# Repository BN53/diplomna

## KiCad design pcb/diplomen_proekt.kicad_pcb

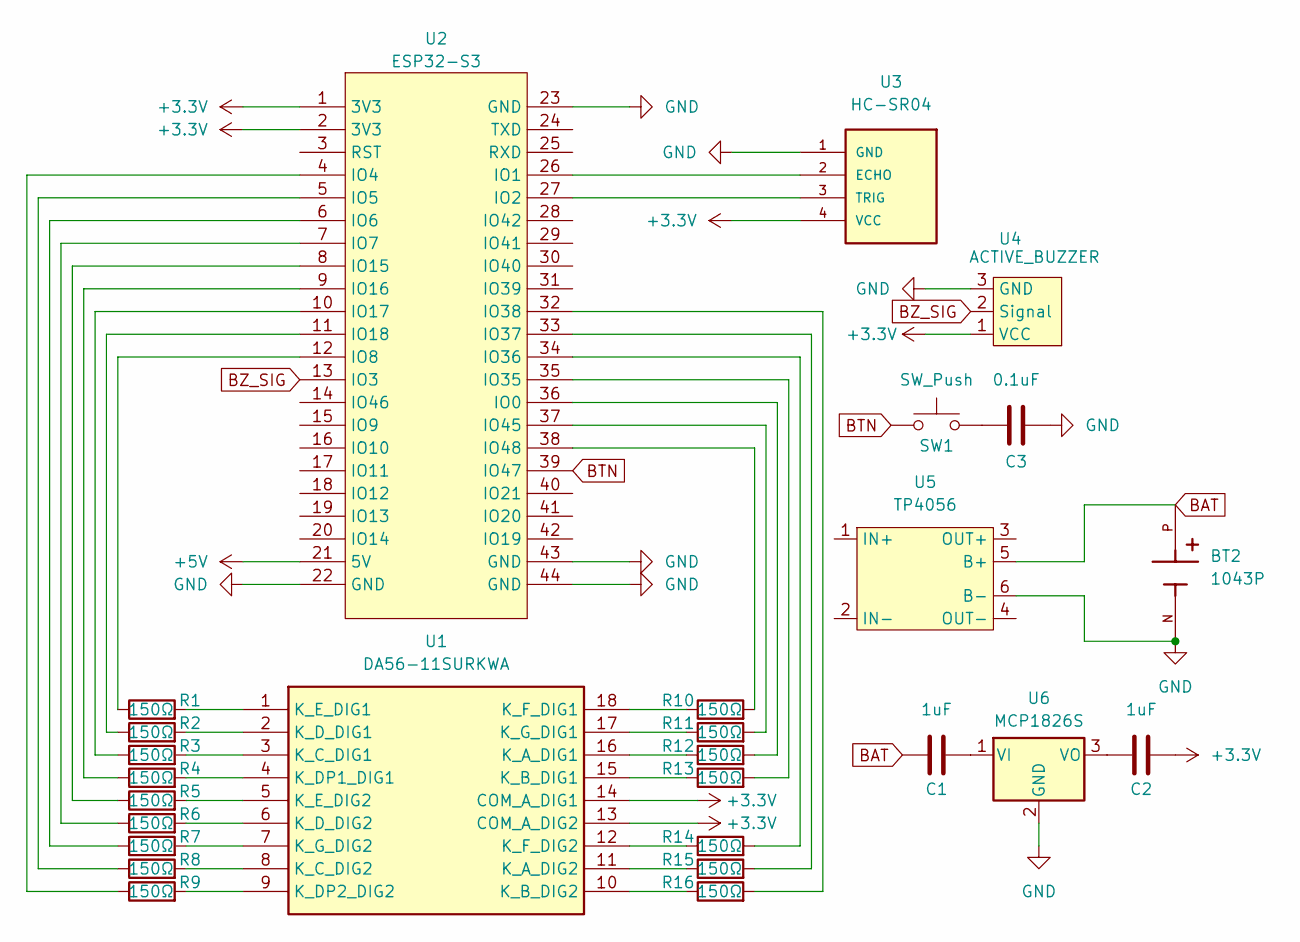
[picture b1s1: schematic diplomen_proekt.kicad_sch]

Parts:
BT2: 1043P; BAT_1043P; PARTREV D
C1, C2: 1uF; CP_Radial_D5.0mm_P2.50mm
C3: 0.1uF; CP_Radial_D5.0mm_P2.50mm
R1, R2, R3, R4, R5, R6, R7, R8, R9, R10, R11, R12, R13, R14, R15, R16: 150Ω; R_Axial_DIN0207_L6.3mm_D2.5mm_P10.16mm_Horizontal
SW1: SW_Push; PinSocket_1x02_P2.54mm_Horizontal
U1: DA56-11SURKWA; DIPS1524W75P254L2500H825Q18N; Manufacturer_Part_Number DA56-11SURKWA; Mouser Part Number 604-DA56-11SURKWA
U2: ESP32-S3; esp32-s3
U3: HC-SR04; PinSocket_1x04_P2.54mm_Horizontal; PARTREV N/A
U4: ACTIVE_BUZZER; PinSocket_1x03_P2.54mm_Horizontal
U5: TP4056; TP4056-18650
U6: MCP1826S; TO254P482X1024X3124-3P

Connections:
+3.3V: C2.2, U1.13 (COM_A_DIG2), U1.14 (COM_A_DIG1), U2.1 (3V3), U2.2 (3V3), U3.4 (VCC), U4.1 (VCC)
+5V: U2.21 (5V)
BAT: BT2.P, C1.1, U5.5 (B+)
BTN: SW1.1, U2.39 (IO47)
BZ_SIG: U2.13 (IO3), U4.2 (Signal)
GND: BT2.N, C3.2, U2.22 (GND), U2.23 (GND), U2.43 (GND), U2.44 (GND), U3.1 (GND), U4.3 (GND), U5.6 (B-), U6.2 (GND)
unnamed: C3.1, SW1.2
unnamed: R12.1, U1.16 (K_A_DIG1)
unnamed: R15.1, U1.11 (K_A_DIG2)
unnamed: R13.1, U1.15 (K_B_DIG1)
unnamed: R16.1, U1.10 (K_B_DIG2)
unnamed: R3.2, U1.3 (K_C_DIG1)
unnamed: R8.2, U1.8 (K_C_DIG2)
unnamed: R4.2, U1.4 (K_DP1_DIG1)
unnamed: R9.2, U1.9 (K_DP2_DIG2)
unnamed: R2.2, U1.2 (K_D_DIG1)
unnamed: R6.2, U1.6 (K_D_DIG2)
unnamed: R1.2, U1.1 (K_E_DIG1)
unnamed: R5.2, U1.5 (K_E_DIG2)
unnamed: R10.1, U1.18 (K_F_DIG1)
unnamed: R14.1, U1.12 (K_F_DIG2)
unnamed: R11.1, U1.17 (K_G_DIG1)
unnamed: R7.2, U1.7 (K_G_DIG2)
unnamed: R12.2, U2.36 (IO0)
unnamed: U2.26 (IO1), U3.2 (ECHO)
unnamed: U2.27 (IO2), U3.3 (TRIG)
unnamed: R9.1, U2.4 (IO4)
unnamed: R8.1, U2.5 (IO5)
unnamed: R7.1, U2.6 (IO6)
unnamed: R6.1, U2.7 (IO7)
unnamed: R1.1, U2.12 (IO8)
unnamed: R5.1, U2.8 (IO15)
unnamed: R4.1, U2.9 (IO16)
unnamed: R3.1, U2.10 (IO17)
unnamed: R2.1, U2.11 (IO18)
unnamed: R13.2, U2.35 (IO35)
unnamed: R14.2, U2.34 (IO36)
unnamed: R15.2, U2.33 (IO37)
unnamed: R16.2, U2.32 (IO38)
unnamed: R11.2, U2.37 (IO45)
unnamed: R10.2, U2.38 (IO48)
unnamed: C1.2, U6.1 (VI)
unnamed: C2.1, U6.3 (VO)

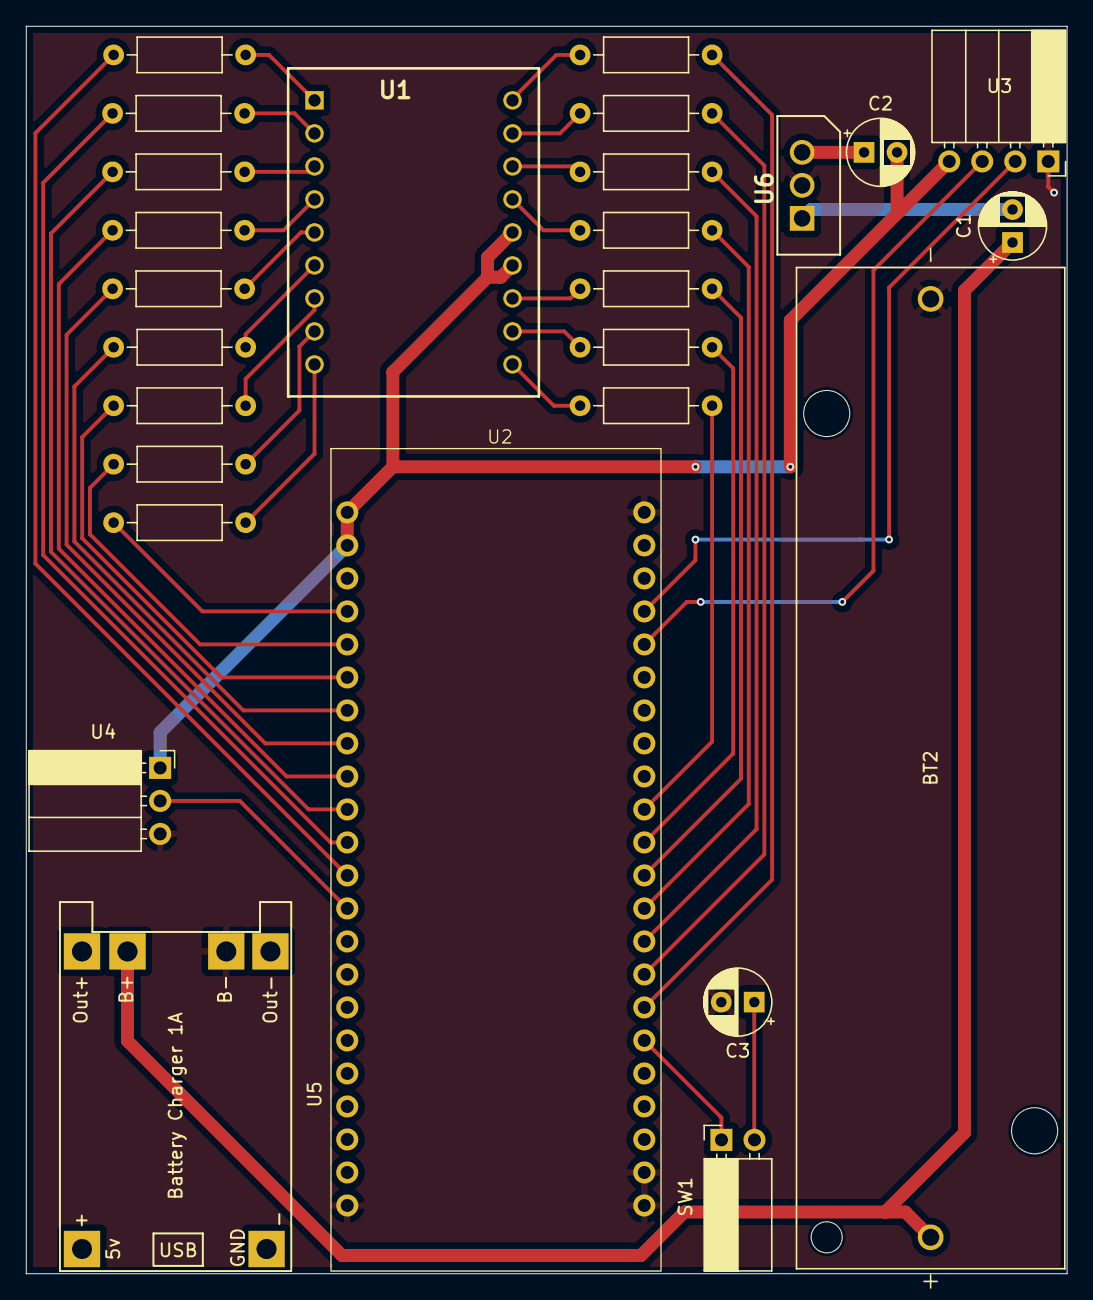
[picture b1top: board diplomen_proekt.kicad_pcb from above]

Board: 2 copper layers, 80.1 x 96.0 mm, 27 parts (0 on the bottom side), 42 nets.

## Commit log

2025-02-20 Fixed directories
2025-02-20 Small changes on the tracks
2025-02-27 Added the code
2025-03-05 Added capacitors
2025-03-05 Optimised button code
2025-03-09 A few optimisations
2025-03-09 Create LICENSE
2025-03-09 Added pcb images
